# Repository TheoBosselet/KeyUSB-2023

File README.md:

# Présentation
Projet de deuxième année de prépa intégrée à Polytech Lille.
Création d'une clé usb du PCB au code, avec la bibliothèque LUFA donnée.

# Etapes de création de la carte 
1. Création du schéma avec KiCad
2. Création du PCB avec KiCad
3. soudage de la carte
4. Test des mémoires 
5. Ajout d'une fonctionnalité ( ICI :  Clé avec un vu mètre qui corrompt les donnés, ainsi qu'un code pour pouvoir accéder au contenu de la clé.) ( En C )
6. Test unitaire

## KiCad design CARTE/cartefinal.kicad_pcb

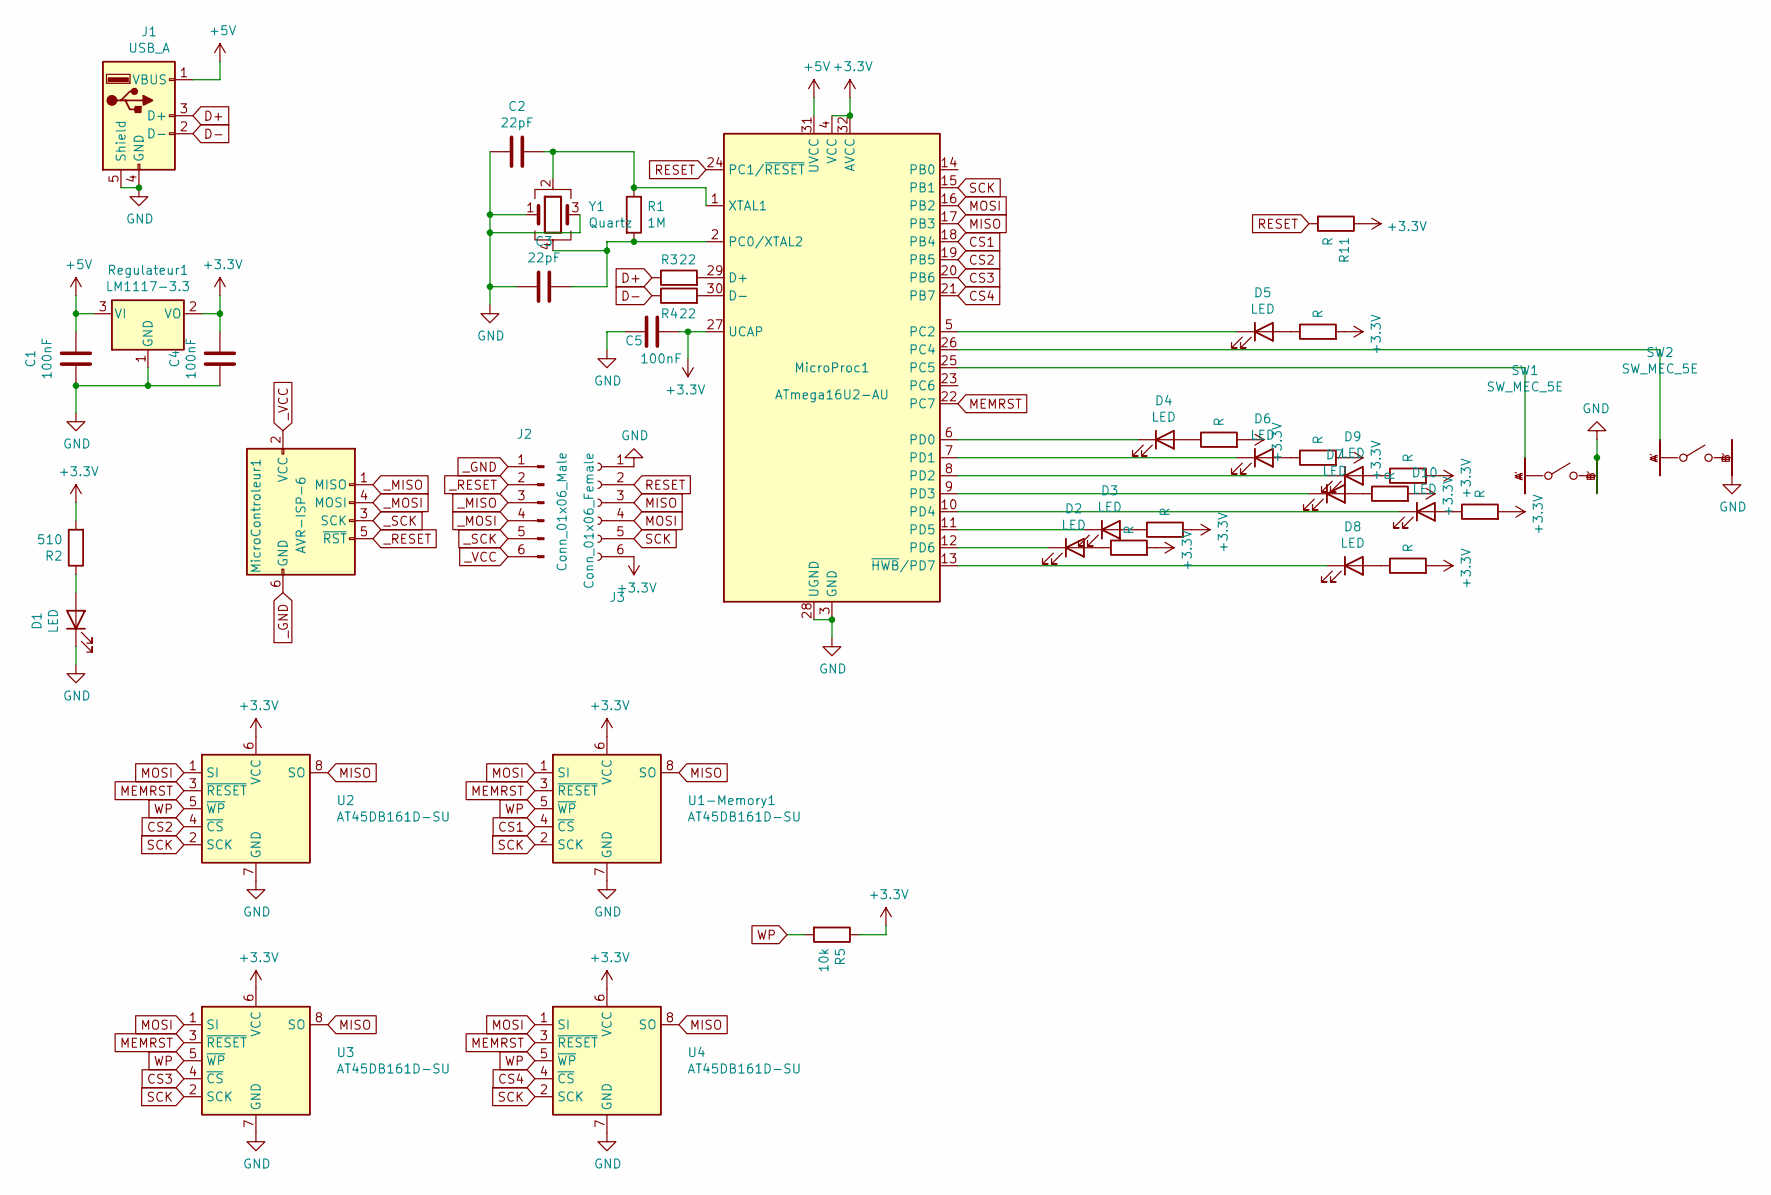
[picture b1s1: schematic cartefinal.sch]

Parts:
C1, C4, C5: 100nF; C_0603_1608Metric_Pad1.08x0.95mm_HandSolder
C2, C3: 22pF; C_0603_1608Metric_Pad1.08x0.95mm_HandSolder
D1, D2, D3, D4, D5, D6, D7, D8, D9, D10: LED; LED_0603_1608Metric_Pad1.05x0.95mm_HandSolder
J1: USB_A; USB_A_CNCTech_1001-011-01101_Horizontal
J2: Conn_01x06_Male; PinHeader_1x06_P2.54mm_Vertical
J3: Conn_01x06_Female; PinHeader_1x06_P2.54mm_Vertical
MicroControleur1: AVR-ISP-6; PinHeader_2x03_P2.54mm_Vertical
MicroProc1: ATmega16U2-AU; TQFP-32_7x7mm_P0.8mm
R1: 1M; R_0603_1608Metric_Pad0.98x0.95mm_HandSolder
R2: 510; R_0603_1608Metric_Pad0.98x0.95mm_HandSolder
R3, R4: 22; R_0603_1608Metric_Pad0.98x0.95mm_HandSolder
R5: 10k; R_0603_1608Metric_Pad0.98x0.95mm_HandSolder
R6, R7, R8, R9, R10, R11, R12, R13, R14, R15: R; R_0603_1608Metric_Pad0.98x0.95mm_HandSolder
Regulateur1: LM1117-3.3; SOT-23
SW1, SW2: SW_MEC_5E; Panasonic_Electronic_Components-EVQ-Q2F01W-MFG
U1-Memory1, U2, U3, U4: AT45DB161D-SU; SOIC-8_5.275x5.275mm_P1.27mm
Y1: Quartz; Crystal_SMD_SeikoEpson_FA238-4Pin_3.2x2.5mm_HandSoldering

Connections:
+3V3: C4.1, C5.1, J3.6, MicroProc1.4 (VCC), MicroProc1.27 (UCAP), MicroProc1.32 (AVCC), R2.2, R5.1, R6.2, R7.2, R8.2, R9.2, R10.2, R11.1, R12.2, R13.2, R14.2, R15.2, Regulateur1.2 (VO), U1-Memory1.6 (VCC), U2.6 (VCC), U3.6 (VCC), U4.6 (VCC); also elsewhere on the board
+5V: C1.1, J1.1 (VBUS), MicroProc1.31 (UVCC), Regulateur1.3 (VI); also elsewhere on the board
CS1: MicroProc1.18 (PB4), U1-Memory1.4 (~CS); also elsewhere on the board
CS2: MicroProc1.19 (PB5), U2.4 (~CS)
CS3: MicroProc1.20 (PB6), U3.4 (~CS)
CS4: MicroProc1.21 (PB7), U4.4 (~CS)
D+: J1.3 (D+), R3.1
D-: J1.2 (D-), R4.1
GND: C1.2, C2.2, C3.2, C4.2, C5.2, D1.1 (K), J1.4 (GND), J1.5 (Shield), J3.1, MicroProc1.3 (GND), MicroProc1.28 (UGND), Regulateur1.1 (GND), SW1.B, SW1.B', SW2.B', U1-Memory1.7 (GND), U2.7 (GND), U3.7 (GND), U4.7 (GND), Y1.1, Y1.3; also elsewhere on the board
MEMRST: MicroProc1.22 (PC7), U1-Memory1.3 (~RESET~), U2.3 (~RESET~), U3.3 (~RESET~), U4.3 (~RESET~); also elsewhere on the board
MISO: J3.3, MicroProc1.17 (PB3), U1-Memory1.8 (SO), U2.8 (SO), U3.8 (SO), U4.8 (SO); also elsewhere on the board
MOSI: J3.4, MicroProc1.16 (PB2), U1-Memory1.1 (SI), U2.1 (SI), U3.1 (SI), U4.1 (SI); also elsewhere on the board
unnamed: C2.1, MicroProc1.1 (XTAL1), R1.1, Y1.2
unnamed: C3.1, MicroProc1.2 (PC0/XTAL2), R1.2, Y1.4
unnamed: D1.2 (A), R2.1
unnamed: D2.1 (K), MicroProc1.12 (PD6)
unnamed: D2.2 (A), R6.1
unnamed: D3.1 (K), MicroProc1.11 (PD5)
unnamed: D3.2 (A), R7.1
unnamed: D4.1 (K), MicroProc1.6 (PD0)
unnamed: D4.2 (A), R8.1
unnamed: D5.1 (K), MicroProc1.5 (PC2)
unnamed: D5.2 (A), R9.1
unnamed: D6.1 (K), MicroProc1.7 (PD1)
unnamed: D6.2 (A), R10.1
unnamed: D7.1 (K), MicroProc1.9 (PD3)
unnamed: D7.2 (A), R12.1
unnamed: D8.1 (K), MicroProc1.13 (~HWB~/PD7)
unnamed: D8.2 (A), R13.1
unnamed: D9.1 (K), MicroProc1.8 (PD2)
unnamed: D9.2 (A), R14.1
unnamed: D10.1 (K), MicroProc1.10 (PD4)
unnamed: D10.2 (A), R15.1
unnamed: MicroProc1.25 (PC5), SW1.A
unnamed: MicroProc1.26 (PC4), SW2.A
unnamed: MicroProc1.29 (D+), R3.2
unnamed: MicroProc1.30 (D-), R4.2
RESET: J3.2, MicroProc1.24 (PC1/~RESET), R11.2
SCK: J3.5, MicroProc1.15 (PB1), U1-Memory1.2 (SCK), U2.2 (SCK), U3.2 (SCK), U4.2 (SCK); also elsewhere on the board
WP: R5.2, U1-Memory1.5 (~WP), U2.5 (~WP), U3.5 (~WP), U4.5 (~WP); also elsewhere on the board
_GND: J2.1, MicroControleur1.6 (GND); also elsewhere on the board
_MISO: J2.3, MicroControleur1.1 (MISO); also elsewhere on the board
_MOSI: J2.4, MicroControleur1.4 (MOSI); also elsewhere on the board
_RESET: J2.2, MicroControleur1.5 (~RST); also elsewhere on the board
_SCK: J2.5, MicroControleur1.3 (SCK); also elsewhere on the board
_VCC: J2.6, MicroControleur1.2 (VCC); also elsewhere on the board

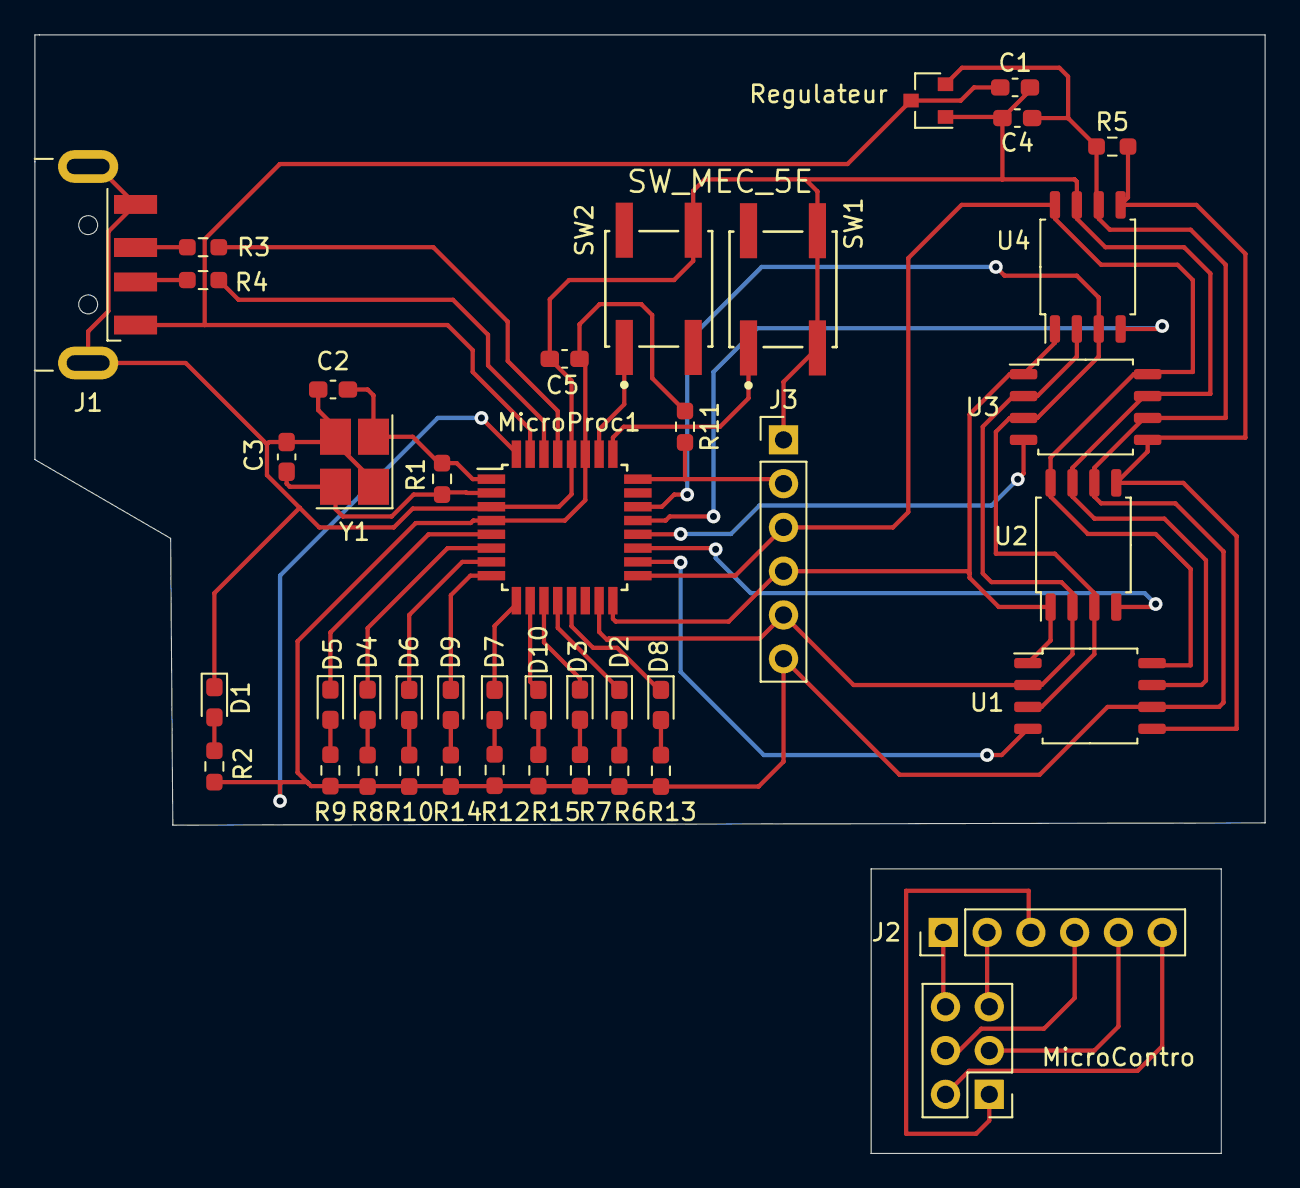
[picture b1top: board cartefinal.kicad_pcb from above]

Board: 2 copper layers, 71.4 x 64.9 mm, 43 parts (0 on the bottom side), 46 nets.

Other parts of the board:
MicroContro: AVR-ISP-6; PinHeader_2x03_P2.54mm_Vertical
Regulateur: LM1117-3.3; SOT-23
U1: AT45DB161D-SU; SOIC-8_5.275x5.275mm_P1.27mm

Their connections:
+3V3: Regulateur.2, U1.6; also elsewhere on the board
+5V: Regulateur.3; also elsewhere on the board
CS1: U1.4; also elsewhere on the board
GND: Regulateur.1, U1.7; also elsewhere on the board
MEMRST: U1.3; also elsewhere on the board
MISO: U1.8; also elsewhere on the board
MOSI: U1.1; also elsewhere on the board
SCK: U1.2; also elsewhere on the board
WP: U1.5; also elsewhere on the board
_GND: MicroContro.6; also elsewhere on the board
_MISO: MicroContro.1; also elsewhere on the board
_MOSI: MicroContro.4; also elsewhere on the board
_RESET: MicroContro.5; also elsewhere on the board
_SCK: MicroContro.3; also elsewhere on the board
_VCC: MicroContro.2; also elsewhere on the board

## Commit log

2023-05-31 Create a
